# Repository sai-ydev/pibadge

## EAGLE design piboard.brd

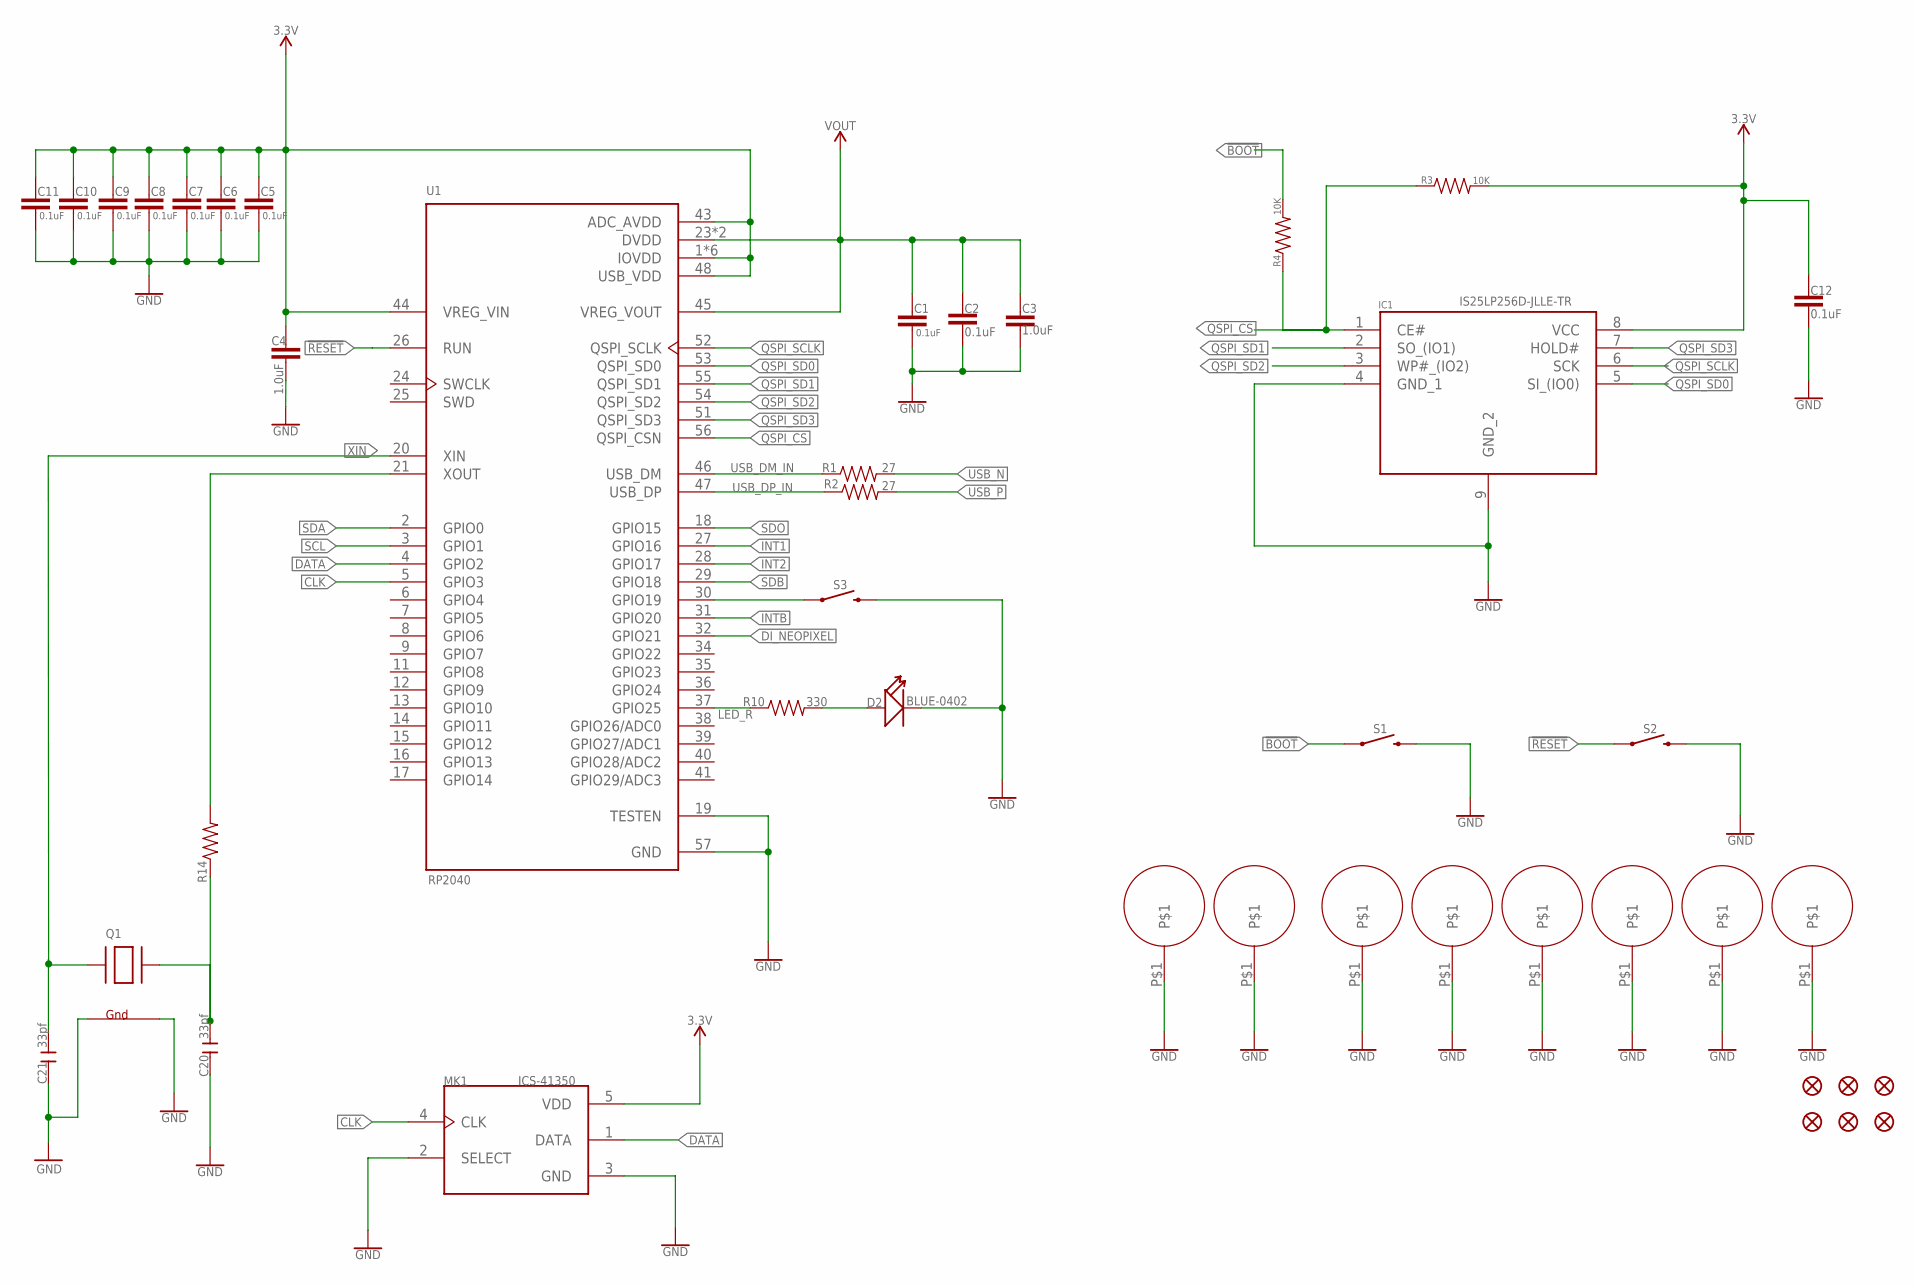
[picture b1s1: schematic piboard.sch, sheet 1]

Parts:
C1, C2, C5, C6, C7, C8, C9, C10, C11, C12: 0.1uF; 0402
C3, C4: 1.0uF; 0402
C20, C21: 33pf; C0402
D2: BLUE-0402; LED-0402
FD1, FD2, FD3, FD4, FD5, FD6: FIDUCIAL1X2; FIDUCIAL-1X2
H1, H2, H3, H4, H5, H6, H7, H8: M25
IC1: IS25LP256D-JLLE-TR; SON127P800X600X80-9N
MK1: ICS-41350; MIC_ICS-41350
Q1: XTAL-4-3225; NX3225
R1, R2: 27; 0402
R3, R4: 10K; 0402
R10: 330; 0402
R14: 0402
S1, S2, S3: MOMENTARY-SWITCH-SPST-SMD-4.6X2.8MM; TACTILE_SWITCH_SMD_4.6X2.8MM
U1: RP2040; QFN40P700X700X90-57N

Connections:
3.3V: C4.1, C5.1, C6.1, C7.1, C8.1, C9.1, C10.1, C11.1, C12.1, IC1.8 (VCC), MK1.5 (VDD), R3.2, U1.1 (IOVDD), U1.10 (IOVDD), U1.22 (IOVDD), U1.33 (IOVDD), U1.42 (IOVDD), U1.43 (ADC_AVDD), U1.44 (VREG_VIN), U1.48 (USB_VDD), U1.49 (IOVDD); also elsewhere on the board
!BOOT: R4.2, S1.1, S1.2 (1)
!RESET: S2.1, S2.2 (1), U1.26 (RUN)
CLK: MK1.4 (CLK), U1.5 (GPIO3)
DATA: MK1.1 (DATA), U1.4 (GPIO2)
DI_NEOPIXEL: U1.32 (GPIO21); also elsewhere on the board
GND: C1.2, C2.2, C3.2, C4.2, C5.2, C6.2, C7.2, C8.2, C9.2, C10.2, C11.2, C12.2, C20.1, C21.1, D2.-, H1.P$1, H2.P$1, H3.P$1, H4.P$1, H5.P$1, H6.P$1, H7.P$1, H8.P$1, IC1.4 (GND_1), IC1.9 (GND_2), MK1.2 (SELECT), MK1.3 (GND), Q1.2 (G2), Q1.4 (G1), S1.3 (2), S1.4 (2), S2.3 (2), S2.4 (2), S3.3 (2), S3.4 (2), U1.19 (TESTEN), U1.57 (GND); also elsewhere on the board
INT1: U1.27 (GPIO16); also elsewhere on the board
INT2: U1.28 (GPIO17); also elsewhere on the board
INTB: U1.31 (GPIO20); also elsewhere on the board
LED_R: R10.1, U1.37 (GPIO25)
unnamed: D2.+, R10.2
unnamed: C20.2, Q1.3 (X2), R14.1
unnamed: R14.2, U1.21 (XOUT)
unnamed: S3.1, S3.2 (1), U1.30 (GPIO19)
QSPI_CS: IC1.1 (CE#), R3.1, R4.1, U1.56 (QSPI_CSN)
QSPI_SCLK: IC1.6 (SCK), U1.52 (QSPI_SCLK)
QSPI_SD0: IC1.5 (SI_(IO0)), U1.53 (QSPI_SD0)
QSPI_SD1: IC1.2 (SO_(IO1)), U1.55 (QSPI_SD1)
QSPI_SD2: IC1.3 (WP#_(IO2)), U1.54 (QSPI_SD2)
QSPI_SD3: IC1.7 (HOLD#), U1.51 (QSPI_SD3)
SCL: U1.3 (GPIO1); also elsewhere on the board
SDA: U1.2 (GPIO0); also elsewhere on the board
SDB: U1.29 (GPIO18); also elsewhere on the board
SDO: U1.18 (GPIO15); also elsewhere on the board
USB_DM_IN: R1.1, U1.46 (USB_DM)
USB_DP_IN: R2.1, U1.47 (USB_DP)
USB_N: R1.2; also elsewhere on the board
USB_P: R2.2; also elsewhere on the board
VOUT: C1.1, C2.1, C3.1, U1.23 (DVDD), U1.45 (VREG_VOUT), U1.50 (DVDD)
XIN: C21.2, Q1.1 (X1), U1.20 (XIN)

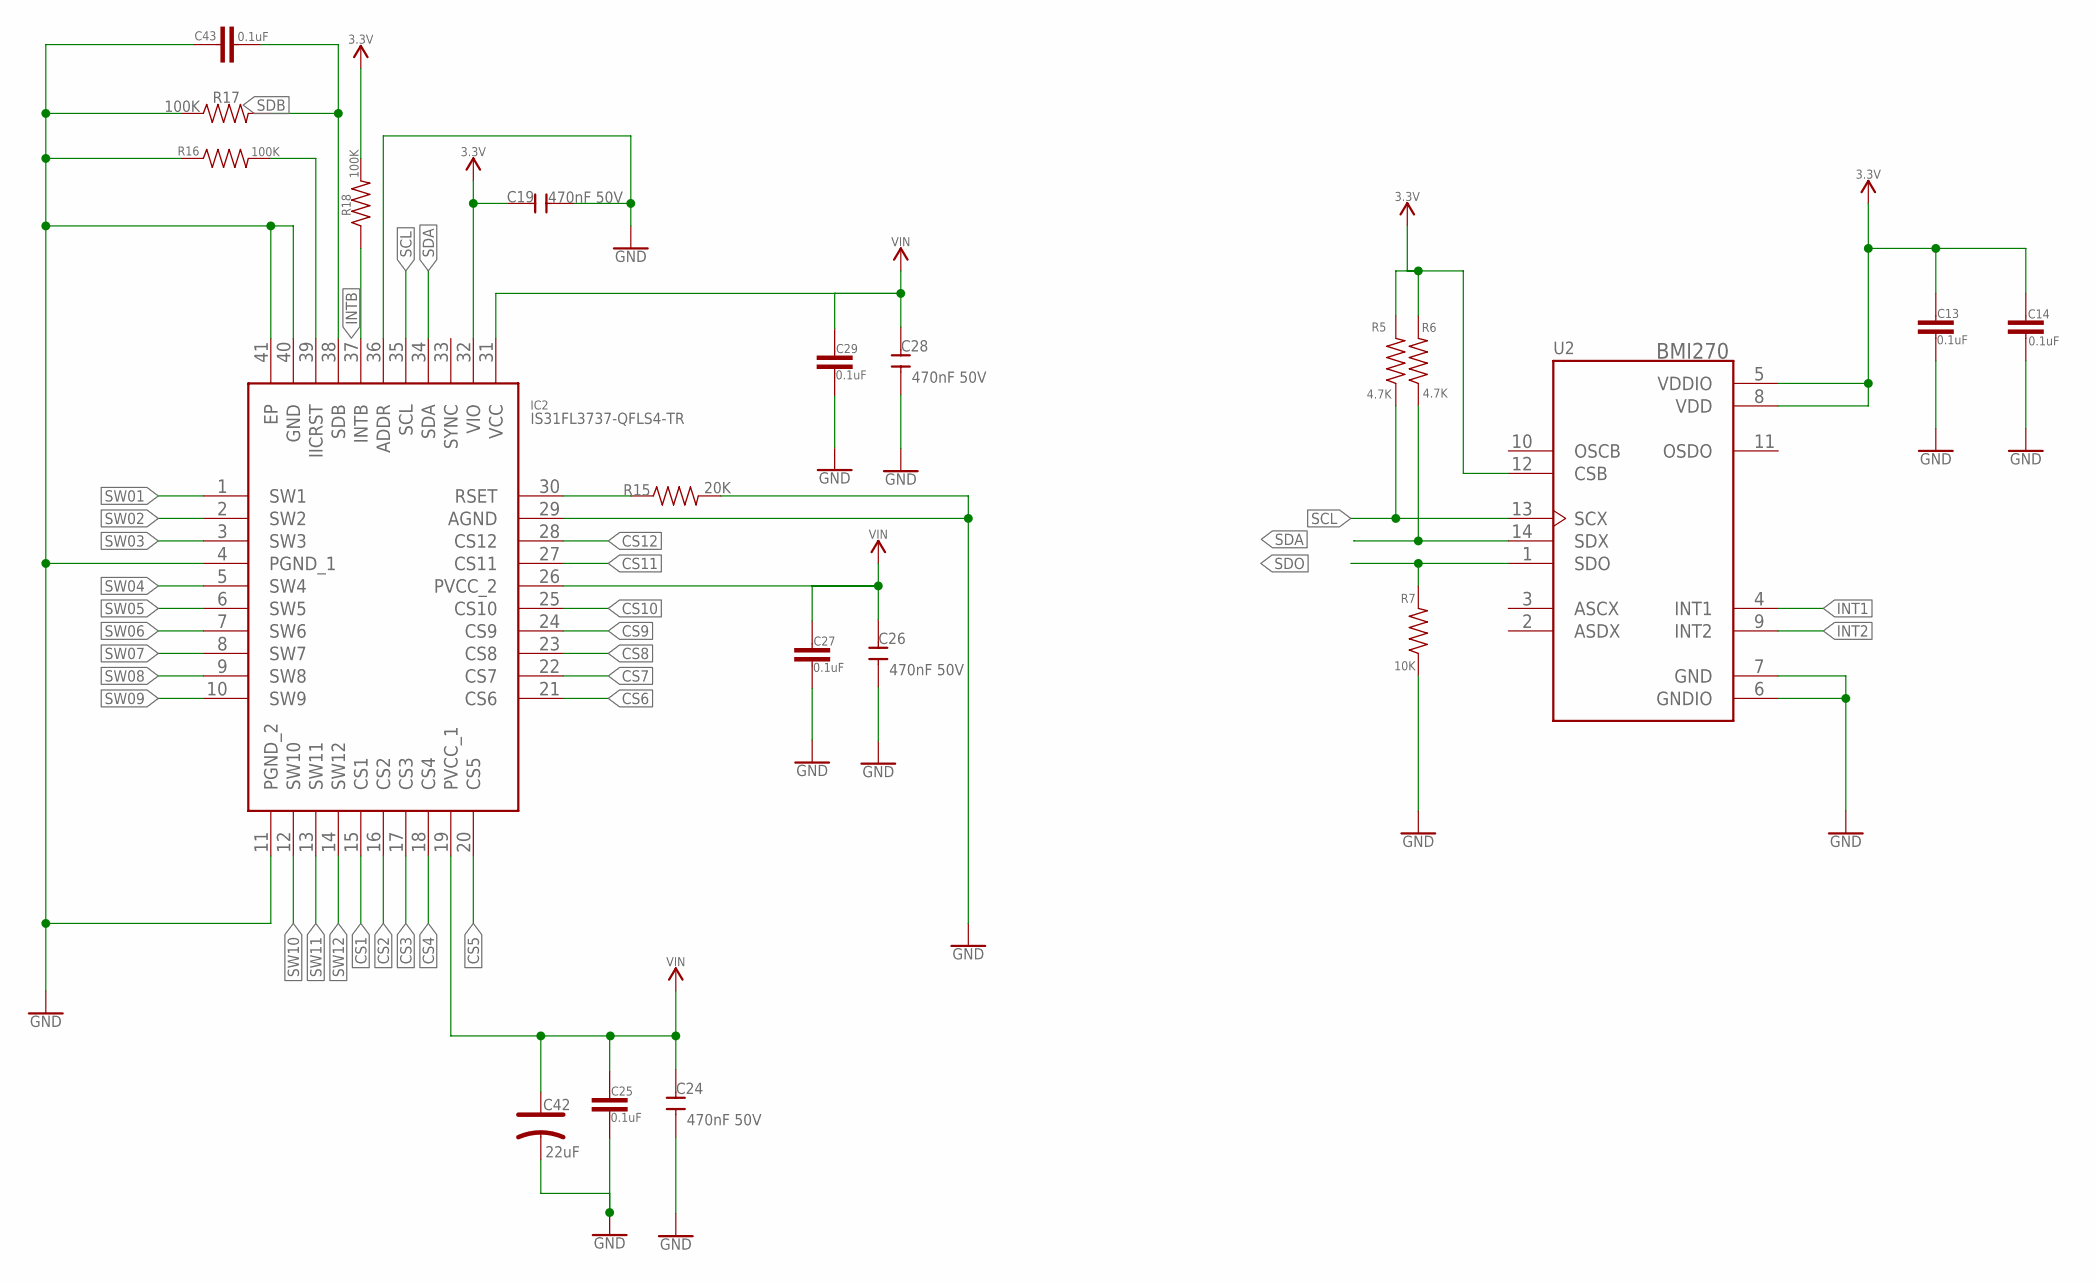
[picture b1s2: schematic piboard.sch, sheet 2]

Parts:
C13, C14, C25, C27, C29, C43: 0.1uF; 0402
C19, C24, C26, C28: 470nF 50V; C0402
C42: 22uF; AVX-A
IC2: IS31FL3737-QFLS4-TR; QFN40P500X500X80-41N
R5, R6: 4.7K; 0402
R7: 10K; 0402
R15: 20K; 0402
R16, R17, R18: 100K; 0402
U2: BMI270; XDCR_BMI270

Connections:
3.3V: C13.1, C14.1, C19.1, IC2.32 (VIO), R5.2, R6.2, R18.2, U2.5 (VDDIO), U2.8 (VDD), U2.12 (CSB); also elsewhere on the board
CS1: IC2.15 (CS1); also elsewhere on the board
CS2: IC2.16 (CS2); also elsewhere on the board
CS3: IC2.17 (CS3); also elsewhere on the board
CS4: IC2.18 (CS4); also elsewhere on the board
CS5: IC2.20 (CS5); also elsewhere on the board
CS6: IC2.21 (CS6); also elsewhere on the board
CS7: IC2.22 (CS7); also elsewhere on the board
CS8: IC2.23 (CS8); also elsewhere on the board
CS9: IC2.24 (CS9); also elsewhere on the board
CS10: IC2.25 (CS10); also elsewhere on the board
CS11: IC2.27 (CS11); also elsewhere on the board
CS12: IC2.28 (CS12); also elsewhere on the board
GND: C13.2, C14.2, C19.2, C24.1, C25.2, C26.1, C27.2, C28.1, C29.2, C42.-, C43.1, IC2.4 (PGND_1), IC2.11 (PGND_2), IC2.29 (AGND), IC2.36 (ADDR), IC2.40 (GND), IC2.41 (EP), R7.1, R15.2, R16.1, R17.1, U2.6 (GNDIO), U2.7 (GND); also elsewhere on the board
INT1: U2.4 (INT1); also elsewhere on the board
INT2: U2.9 (INT2); also elsewhere on the board
INTB: IC2.37 (INTB), R18.1; also elsewhere on the board
unnamed: IC2.30 (RSET), R15.1
unnamed: IC2.39 (IICRST), R16.2
SCL: IC2.35 (SCL), R5.1, U2.13 (SCX); also elsewhere on the board
SDA: IC2.34 (SDA), R6.1, U2.14 (SDX); also elsewhere on the board
SDB: C43.2, IC2.38 (SDB), R17.2; also elsewhere on the board
SDO: R7.2, U2.1 (SDO); also elsewhere on the board
SW01: IC2.1 (SW1); also elsewhere on the board
SW02: IC2.2 (SW2); also elsewhere on the board
SW03: IC2.3 (SW3); also elsewhere on the board
SW04: IC2.5 (SW4); also elsewhere on the board
SW05: IC2.6 (SW5); also elsewhere on the board
SW06: IC2.7 (SW6); also elsewhere on the board
SW07: IC2.8 (SW7); also elsewhere on the board
SW08: IC2.9 (SW8); also elsewhere on the board
SW09: IC2.10 (SW9); also elsewhere on the board
SW10: IC2.12 (SW10); also elsewhere on the board
SW11: IC2.13 (SW11); also elsewhere on the board
SW12: IC2.14 (SW12); also elsewhere on the board
VIN: C24.2, C25.1, C26.2, C27.1, C28.2, C29.1, C42.+, IC2.19 (PVCC_1), IC2.26 (PVCC_2), IC2.31 (VCC); also elsewhere on the board

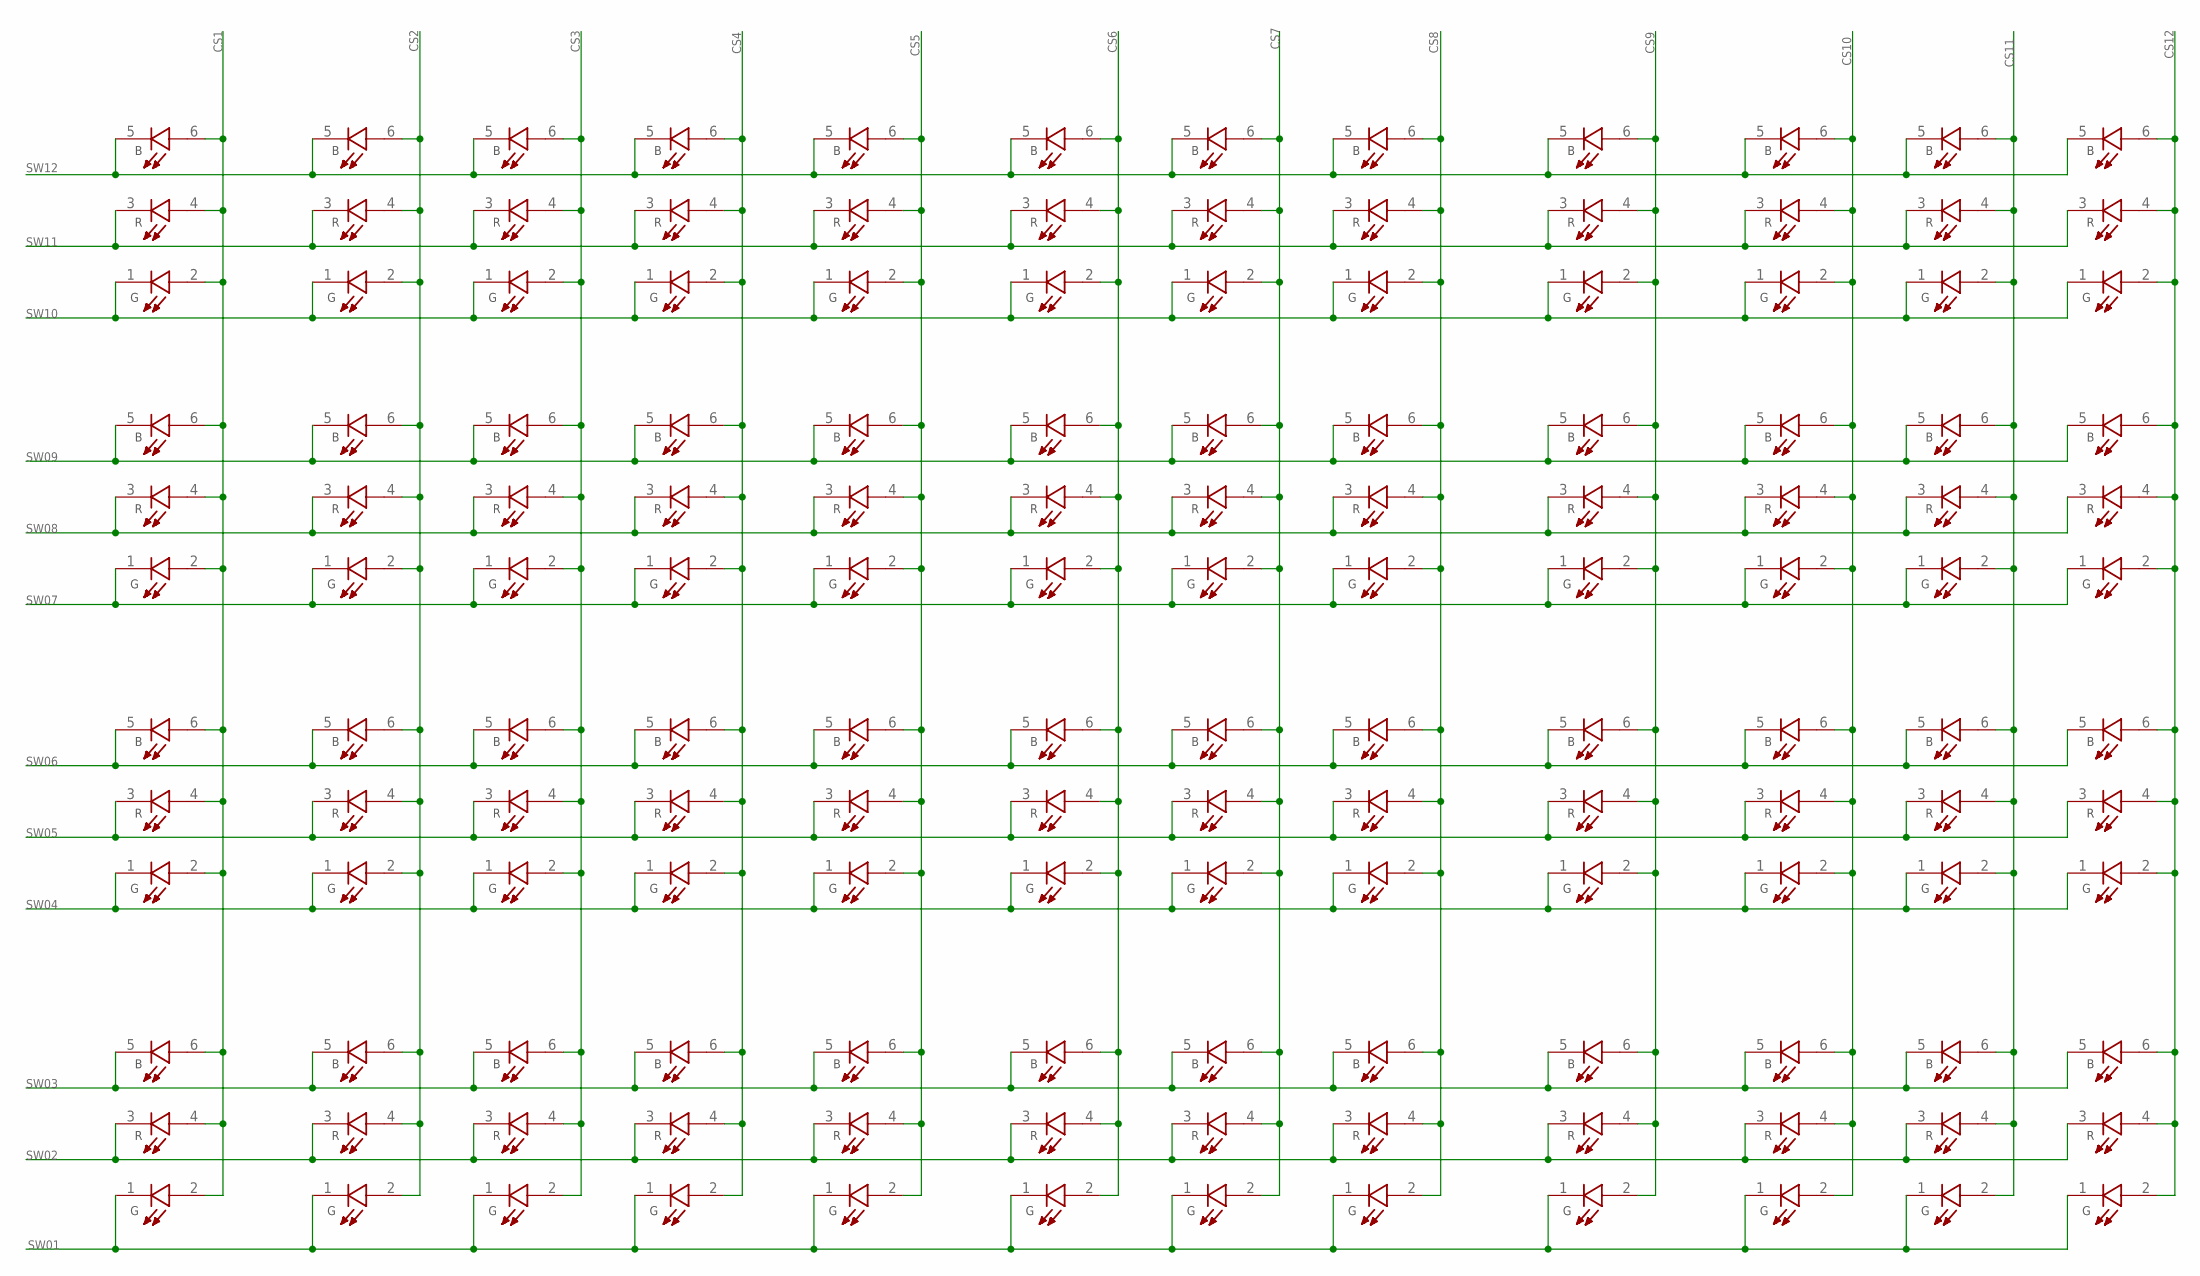
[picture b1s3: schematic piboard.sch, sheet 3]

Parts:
RGB1, RGB2, RGB3, RGB4, RGB5, RGB6, RGB7, RGB8, RGB9, RGB10, RGB11, RGB12, RGB13, RGB14, RGB15, RGB16, RGB17, RGB18, RGB19, RGB20, RGB21, RGB22, RGB23, RGB24, RGB25, RGB26, RGB27, RGB28, RGB29, RGB30, RGB31, RGB32, RGB33, RGB34, RGB35, RGB36, RGB37, RGB38, RGB39, RGB40, RGB41, RGB42, RGB43, RGB44, RGB45, RGB46, RGB47, RGB48: 19-337C/RSBHGHC-A88/4T; LED_19-337C/RSBHGHC-A88/4T

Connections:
CS1: RGB1.2 (G_A), RGB1.4 (R_A), RGB1.6 (B_A), RGB13.2 (G_A), RGB13.4 (R_A), RGB13.6 (B_A), RGB25.2 (G_A), RGB25.4 (R_A), RGB25.6 (B_A), RGB37.2 (G_A), RGB37.4 (R_A), RGB37.6 (B_A); also elsewhere on the board
CS2: RGB2.2 (G_A), RGB2.4 (R_A), RGB2.6 (B_A), RGB14.2 (G_A), RGB14.4 (R_A), RGB14.6 (B_A), RGB26.2 (G_A), RGB26.4 (R_A), RGB26.6 (B_A), RGB38.2 (G_A), RGB38.4 (R_A), RGB38.6 (B_A); also elsewhere on the board
CS3: RGB3.2 (G_A), RGB3.4 (R_A), RGB3.6 (B_A), RGB15.2 (G_A), RGB15.4 (R_A), RGB15.6 (B_A), RGB27.2 (G_A), RGB27.4 (R_A), RGB27.6 (B_A), RGB39.2 (G_A), RGB39.4 (R_A), RGB39.6 (B_A); also elsewhere on the board
CS4: RGB4.2 (G_A), RGB4.4 (R_A), RGB4.6 (B_A), RGB16.2 (G_A), RGB16.4 (R_A), RGB16.6 (B_A), RGB28.2 (G_A), RGB28.4 (R_A), RGB28.6 (B_A), RGB40.2 (G_A), RGB40.4 (R_A), RGB40.6 (B_A); also elsewhere on the board
CS5: RGB5.2 (G_A), RGB5.4 (R_A), RGB5.6 (B_A), RGB17.2 (G_A), RGB17.4 (R_A), RGB17.6 (B_A), RGB29.2 (G_A), RGB29.4 (R_A), RGB29.6 (B_A), RGB41.2 (G_A), RGB41.4 (R_A), RGB41.6 (B_A); also elsewhere on the board
CS6: RGB6.2 (G_A), RGB6.4 (R_A), RGB6.6 (B_A), RGB18.2 (G_A), RGB18.4 (R_A), RGB18.6 (B_A), RGB30.2 (G_A), RGB30.4 (R_A), RGB30.6 (B_A), RGB42.2 (G_A), RGB42.4 (R_A), RGB42.6 (B_A); also elsewhere on the board
CS7: RGB7.2 (G_A), RGB7.4 (R_A), RGB7.6 (B_A), RGB19.2 (G_A), RGB19.4 (R_A), RGB19.6 (B_A), RGB31.2 (G_A), RGB31.4 (R_A), RGB31.6 (B_A), RGB43.2 (G_A), RGB43.4 (R_A), RGB43.6 (B_A); also elsewhere on the board
CS8: RGB8.2 (G_A), RGB8.4 (R_A), RGB8.6 (B_A), RGB20.2 (G_A), RGB20.4 (R_A), RGB20.6 (B_A), RGB32.2 (G_A), RGB32.4 (R_A), RGB32.6 (B_A), RGB44.2 (G_A), RGB44.4 (R_A), RGB44.6 (B_A); also elsewhere on the board
CS9: RGB9.2 (G_A), RGB9.4 (R_A), RGB9.6 (B_A), RGB21.2 (G_A), RGB21.4 (R_A), RGB21.6 (B_A), RGB33.2 (G_A), RGB33.4 (R_A), RGB33.6 (B_A), RGB45.2 (G_A), RGB45.4 (R_A), RGB45.6 (B_A); also elsewhere on the board
CS10: RGB10.2 (G_A), RGB10.4 (R_A), RGB10.6 (B_A), RGB22.2 (G_A), RGB22.4 (R_A), RGB22.6 (B_A), RGB34.2 (G_A), RGB34.4 (R_A), RGB34.6 (B_A), RGB46.2 (G_A), RGB46.4 (R_A), RGB46.6 (B_A); also elsewhere on the board
CS11: RGB11.2 (G_A), RGB11.4 (R_A), RGB11.6 (B_A), RGB23.2 (G_A), RGB23.4 (R_A), RGB23.6 (B_A), RGB35.2 (G_A), RGB35.4 (R_A), RGB35.6 (B_A), RGB47.2 (G_A), RGB47.4 (R_A), RGB47.6 (B_A); also elsewhere on the board
CS12: RGB12.2 (G_A), RGB12.4 (R_A), RGB12.6 (B_A), RGB24.2 (G_A), RGB24.4 (R_A), RGB24.6 (B_A), RGB36.2 (G_A), RGB36.4 (R_A), RGB36.6 (B_A), RGB48.2 (G_A), RGB48.4 (R_A), RGB48.6 (B_A); also elsewhere on the board
SW01: RGB37.1 (G_C), RGB38.1 (G_C), RGB39.1 (G_C), RGB40.1 (G_C), RGB41.1 (G_C), RGB42.1 (G_C), RGB43.1 (G_C), RGB44.1 (G_C), RGB45.1 (G_C), RGB46.1 (G_C), RGB47.1 (G_C), RGB48.1 (G_C); also elsewhere on the board
SW02: RGB37.3 (R_C), RGB38.3 (R_C), RGB39.3 (R_C), RGB40.3 (R_C), RGB41.3 (R_C), RGB42.3 (R_C), RGB43.3 (R_C), RGB44.3 (R_C), RGB45.3 (R_C), RGB46.3 (R_C), RGB47.3 (R_C), RGB48.3 (R_C); also elsewhere on the board
SW03: RGB37.5 (B_C), RGB38.5 (B_C), RGB39.5 (B_C), RGB40.5 (B_C), RGB41.5 (B_C), RGB42.5 (B_C), RGB43.5 (B_C), RGB44.5 (B_C), RGB45.5 (B_C), RGB46.5 (B_C), RGB47.5 (B_C), RGB48.5 (B_C); also elsewhere on the board
SW04: RGB25.1 (G_C), RGB26.1 (G_C), RGB27.1 (G_C), RGB28.1 (G_C), RGB29.1 (G_C), RGB30.1 (G_C), RGB31.1 (G_C), RGB32.1 (G_C), RGB33.1 (G_C), RGB34.1 (G_C), RGB35.1 (G_C), RGB36.1 (G_C); also elsewhere on the board
SW05: RGB25.3 (R_C), RGB26.3 (R_C), RGB27.3 (R_C), RGB28.3 (R_C), RGB29.3 (R_C), RGB30.3 (R_C), RGB31.3 (R_C), RGB32.3 (R_C), RGB33.3 (R_C), RGB34.3 (R_C), RGB35.3 (R_C), RGB36.3 (R_C); also elsewhere on the board
SW06: RGB25.5 (B_C), RGB26.5 (B_C), RGB27.5 (B_C), RGB28.5 (B_C), RGB29.5 (B_C), RGB30.5 (B_C), RGB31.5 (B_C), RGB32.5 (B_C), RGB33.5 (B_C), RGB34.5 (B_C), RGB35.5 (B_C), RGB36.5 (B_C); also elsewhere on the board
SW07: RGB13.1 (G_C), RGB14.1 (G_C), RGB15.1 (G_C), RGB16.1 (G_C), RGB17.1 (G_C), RGB18.1 (G_C), RGB19.1 (G_C), RGB20.1 (G_C), RGB21.1 (G_C), RGB22.1 (G_C), RGB23.1 (G_C), RGB24.1 (G_C); also elsewhere on the board
SW08: RGB13.3 (R_C), RGB14.3 (R_C), RGB15.3 (R_C), RGB16.3 (R_C), RGB17.3 (R_C), RGB18.3 (R_C), RGB19.3 (R_C), RGB20.3 (R_C), RGB21.3 (R_C), RGB22.3 (R_C), RGB23.3 (R_C), RGB24.3 (R_C); also elsewhere on the board
SW09: RGB13.5 (B_C), RGB14.5 (B_C), RGB15.5 (B_C), RGB16.5 (B_C), RGB17.5 (B_C), RGB18.5 (B_C), RGB19.5 (B_C), RGB20.5 (B_C), RGB21.5 (B_C), RGB22.5 (B_C), RGB23.5 (B_C), RGB24.5 (B_C); also elsewhere on the board
SW10: RGB1.1 (G_C), RGB2.1 (G_C), RGB3.1 (G_C), RGB4.1 (G_C), RGB5.1 (G_C), RGB6.1 (G_C), RGB7.1 (G_C), RGB8.1 (G_C), RGB9.1 (G_C), RGB10.1 (G_C), RGB11.1 (G_C), RGB12.1 (G_C); also elsewhere on the board
SW11: RGB1.3 (R_C), RGB2.3 (R_C), RGB3.3 (R_C), RGB4.3 (R_C), RGB5.3 (R_C), RGB6.3 (R_C), RGB7.3 (R_C), RGB8.3 (R_C), RGB9.3 (R_C), RGB10.3 (R_C), RGB11.3 (R_C), RGB12.3 (R_C); also elsewhere on the board
SW12: RGB1.5 (B_C), RGB2.5 (B_C), RGB3.5 (B_C), RGB4.5 (B_C), RGB5.5 (B_C), RGB6.5 (B_C), RGB7.5 (B_C), RGB8.5 (B_C), RGB9.5 (B_C), RGB10.5 (B_C), RGB11.5 (B_C), RGB12.5 (B_C); also elsewhere on the board

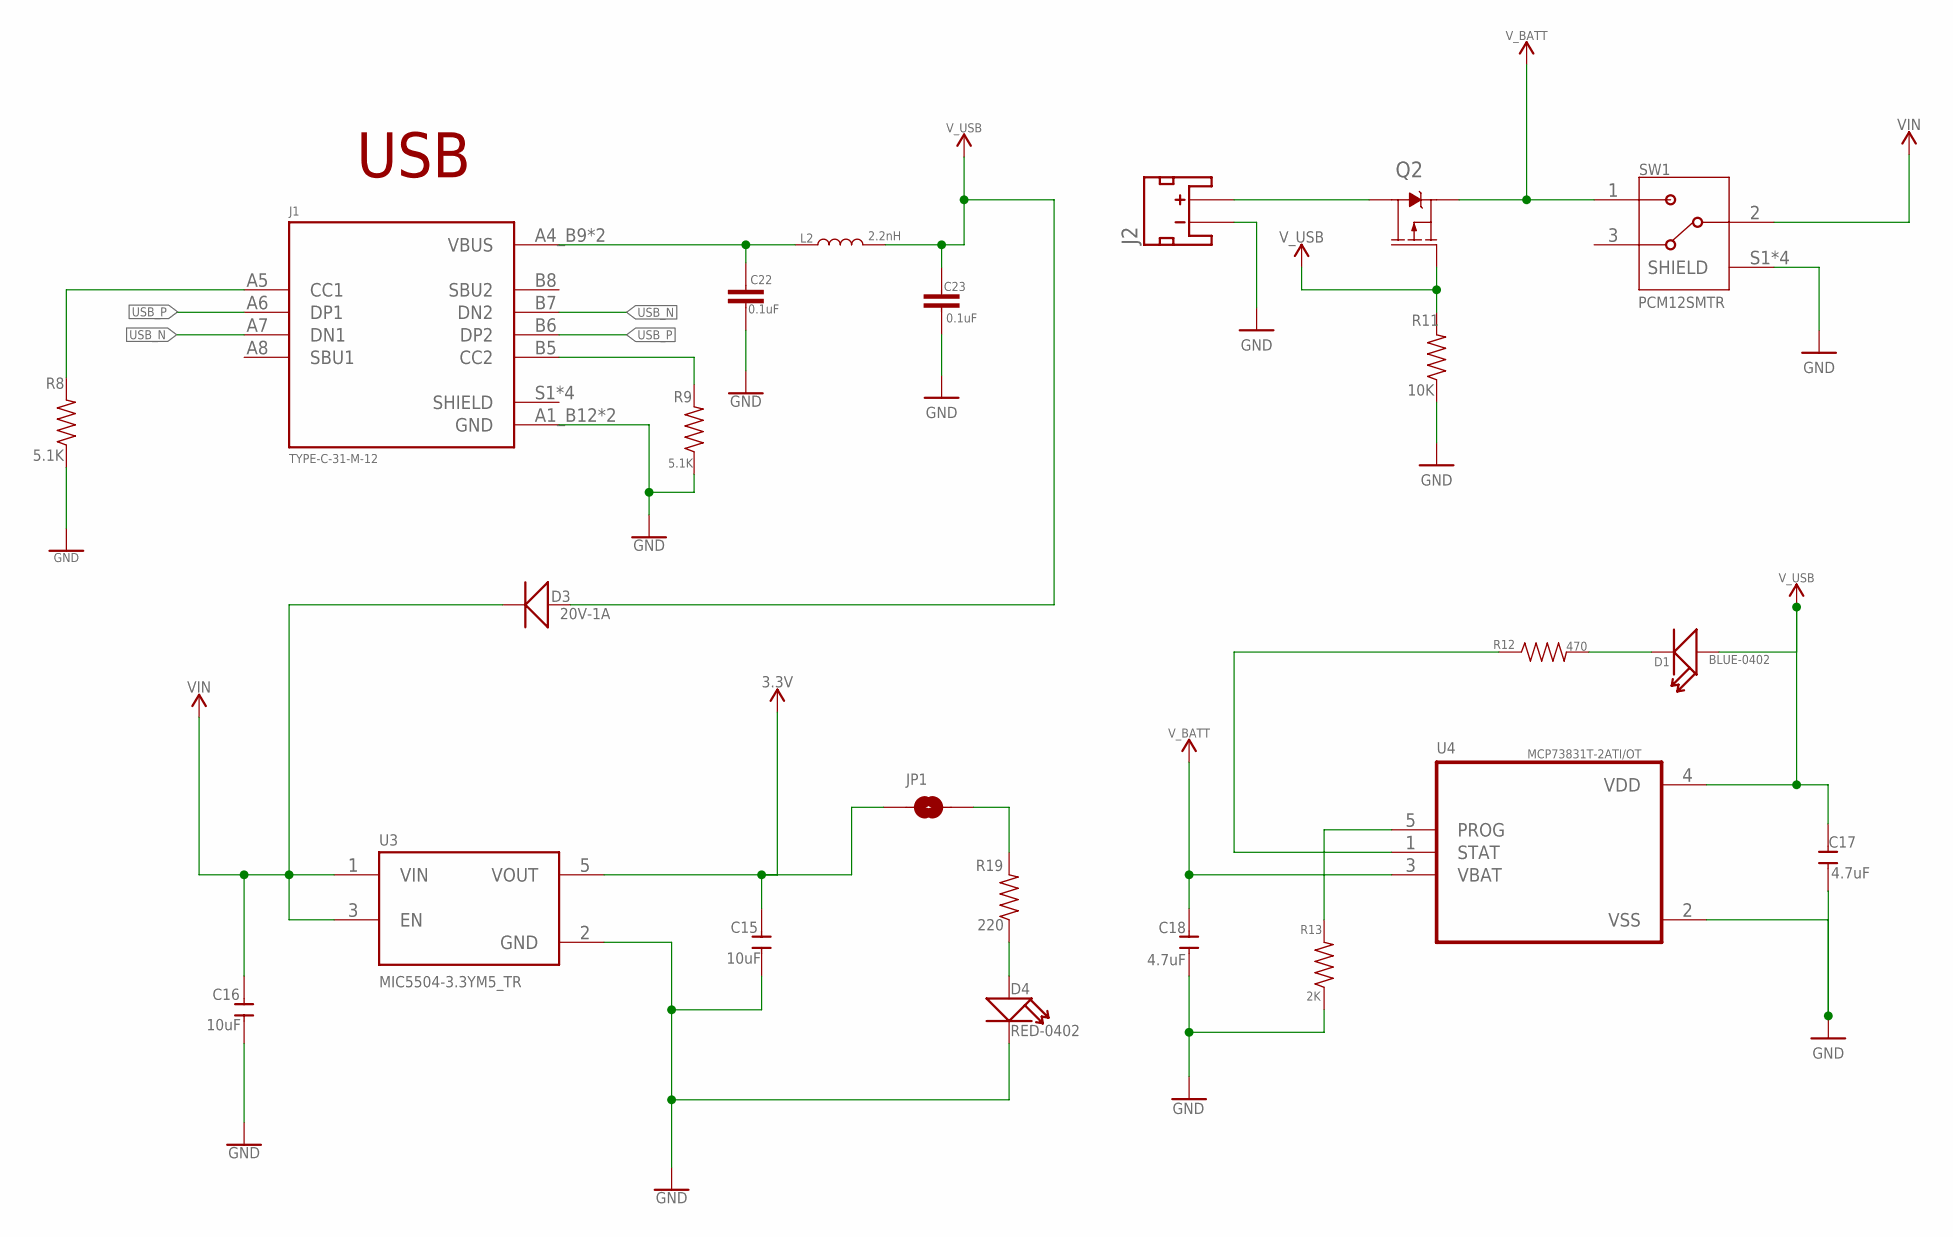
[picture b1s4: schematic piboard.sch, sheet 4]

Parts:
C15, C16: 10uF; C0402
C17, C18: 4.7uF; C0402
C22, C23: 0.1uF; 0402
D1: BLUE-0402; LED-0402
D3: 20V-1A; SOD-123
D4: RED-0402; LED-0402
J1: TYPE-C-31-M-12; HRO_TYPE-C-31-M-12
J2: JST_2MM_MALE; JST-2-SMD
JP1: JUMPER-SMT_2_NO_SILK_ROUND; SMT-JUMPER_2_NO_SILK_ROUND
L2: 2.2nH; 0402
Q2: 2.5A/30V/105mΩ; SOT23-3
R8, R9: 5.1K; 0402
R11: 10K; 0402
R12: 470; 0402
R13: 2K; 0402
R19: 220; 0402
SW1: PCM12SMTR; SW_PCM12SMTR
U3: MIC5504-3.3YM5_TR; SOT95P280X145-5N
U4: MCP73831T-2ATI/OT; SOT95P280X145-5N

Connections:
3.3V: C15.2, JP1.1, U3.5 (VOUT); also elsewhere on the board
GND: C15.1, C16.1, C17.1, C18.1, C22.2, C23.2, D4.-, J1.A1_B12 (GND), J1.B1_A12 (GND), J2.1 (-), R8.1, R9.1, R11.1, R13.1, SW1.S1 (SHIELD), SW1.S2 (SHIELD), SW1.S3 (SHIELD), SW1.S4 (SHIELD), U3.2 (GND), U4.2 (VSS); also elsewhere on the board
unnamed: J1.A5 (CC1), R8.2
unnamed: J1.B5 (CC2), R9.2
unnamed: J2.2 (+), Q2.3 (D)
unnamed: D1.-, R12.2
unnamed: R12.1, U4.1 (STAT)
unnamed: C22.1, J1.A4_B9 (VBUS), J1.B4_A9 (VBUS), L2.1
unnamed: R13.2, U4.5 (PROG)
unnamed: D4.+, R19.1
unnamed: JP1.2, R19.2
USB_N: J1.A7 (DN1), J1.B7 (DN2); also elsewhere on the board
USB_P: J1.A6 (DP1), J1.B6 (DP2); also elsewhere on the board
VIN: C16.2, D3.-, SW1.2, U3.1 (VIN), U3.3 (EN); also elsewhere on the board
V_BATT: C18.2, Q2.2 (S), SW1.1, U4.3 (VBAT)
V_USB: C17.2, C23.1, D1.+, D3.+, L2.2, Q2.1 (G), R11.2, U4.4 (VDD)

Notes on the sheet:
USB

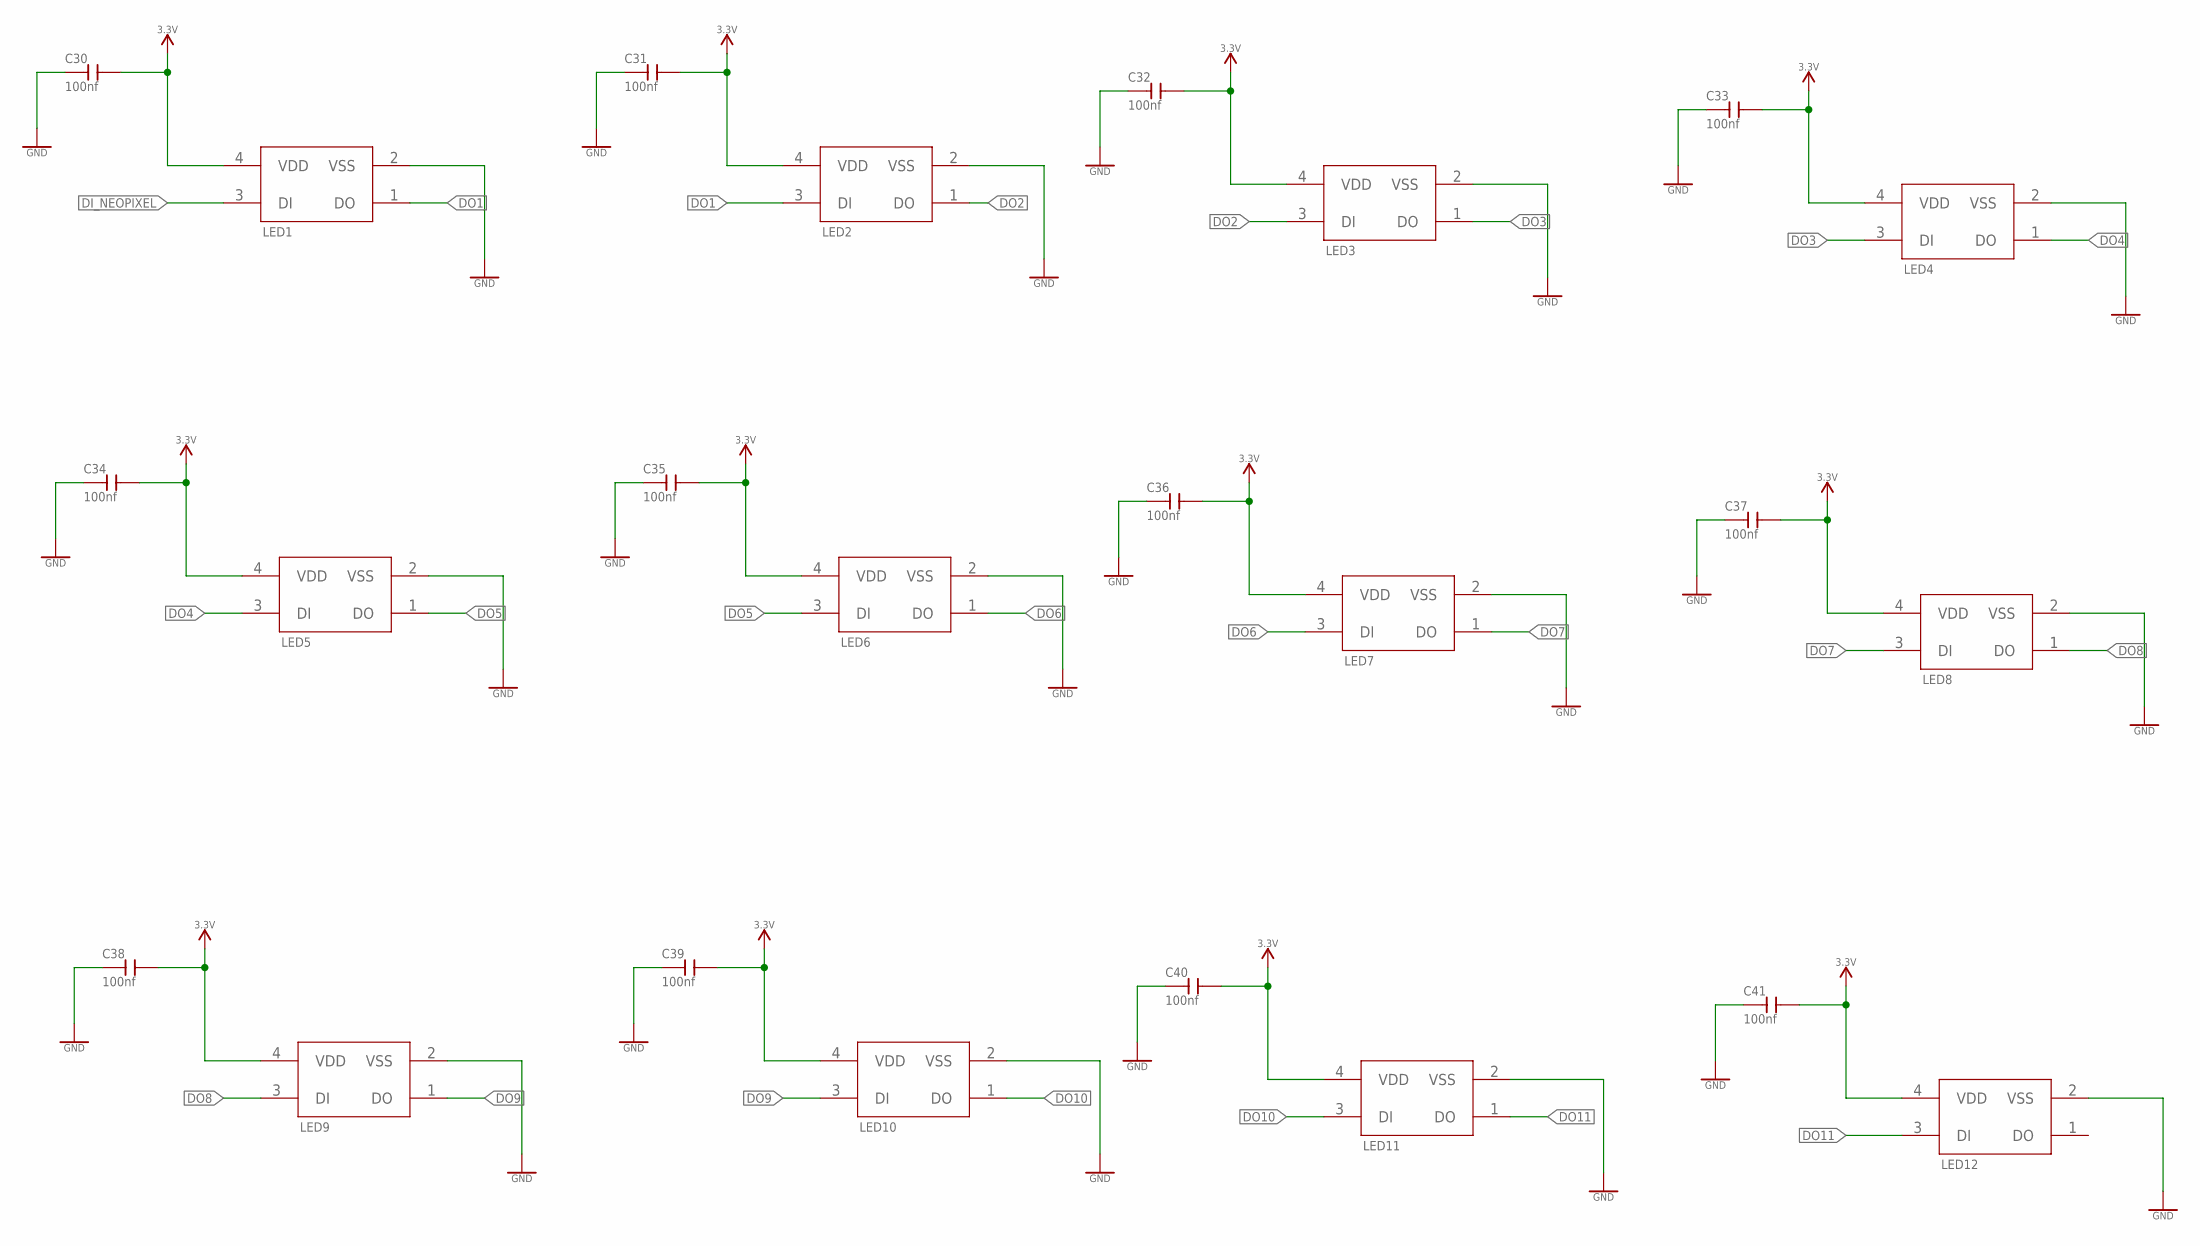
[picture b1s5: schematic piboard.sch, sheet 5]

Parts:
C30, C31, C32, C33, C34, C35, C36, C37, C38, C39, C40, C41: 100nf; C0402
LED1, LED2, LED3, LED4, LED5, LED6, LED7, LED8, LED9, LED10, LED11, LED12: WS2812B-2020

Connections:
3.3V: C30.2, C31.2, C32.2, C33.2, C34.2, C35.2, C36.2, C37.2, C38.2, C39.2, C40.2, C41.2, LED1.4 (VDD), LED2.4 (VDD), LED3.4 (VDD), LED4.4 (VDD), LED5.4 (VDD), LED6.4 (VDD), LED7.4 (VDD), LED8.4 (VDD), LED9.4 (VDD), LED10.4 (VDD), LED11.4 (VDD), LED12.4 (VDD); also elsewhere on the board
DI_NEOPIXEL: LED1.3 (DI); also elsewhere on the board
DO1: LED1.1 (DO), LED2.3 (DI)
DO2: LED2.1 (DO), LED3.3 (DI)
DO3: LED3.1 (DO), LED4.3 (DI)
DO4: LED4.1 (DO), LED5.3 (DI)
DO5: LED5.1 (DO), LED6.3 (DI)
DO6: LED6.1 (DO), LED7.3 (DI)
DO7: LED7.1 (DO), LED8.3 (DI)
DO8: LED8.1 (DO), LED9.3 (DI)
DO9: LED9.1 (DO), LED10.3 (DI)
DO10: LED10.1 (DO), LED11.3 (DI)
DO11: LED11.1 (DO), LED12.3 (DI)
GND: C30.1, C31.1, C32.1, C33.1, C34.1, C35.1, C36.1, C37.1, C38.1, C39.1, C40.1, C41.1, LED1.2 (VSS), LED2.2 (VSS), LED3.2 (VSS), LED4.2 (VSS), LED5.2 (VSS), LED6.2 (VSS), LED7.2 (VSS), LED8.2 (VSS), LED9.2 (VSS), LED10.2 (VSS), LED11.2 (VSS), LED12.2 (VSS); also elsewhere on the board

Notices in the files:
parts and their libraries:
SparkFun-Aesthetics: Licensing: Creative Commons ShareAlike 4.0 International - https://creativecommons.org/licenses/by-sa/4.0
